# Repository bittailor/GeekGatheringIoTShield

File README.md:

Geek Gathering IoT Shield
==========================

Arduino Sketch and hardware designs (Eagle schematic and board) for the Geek Gathering IoT Shield node.

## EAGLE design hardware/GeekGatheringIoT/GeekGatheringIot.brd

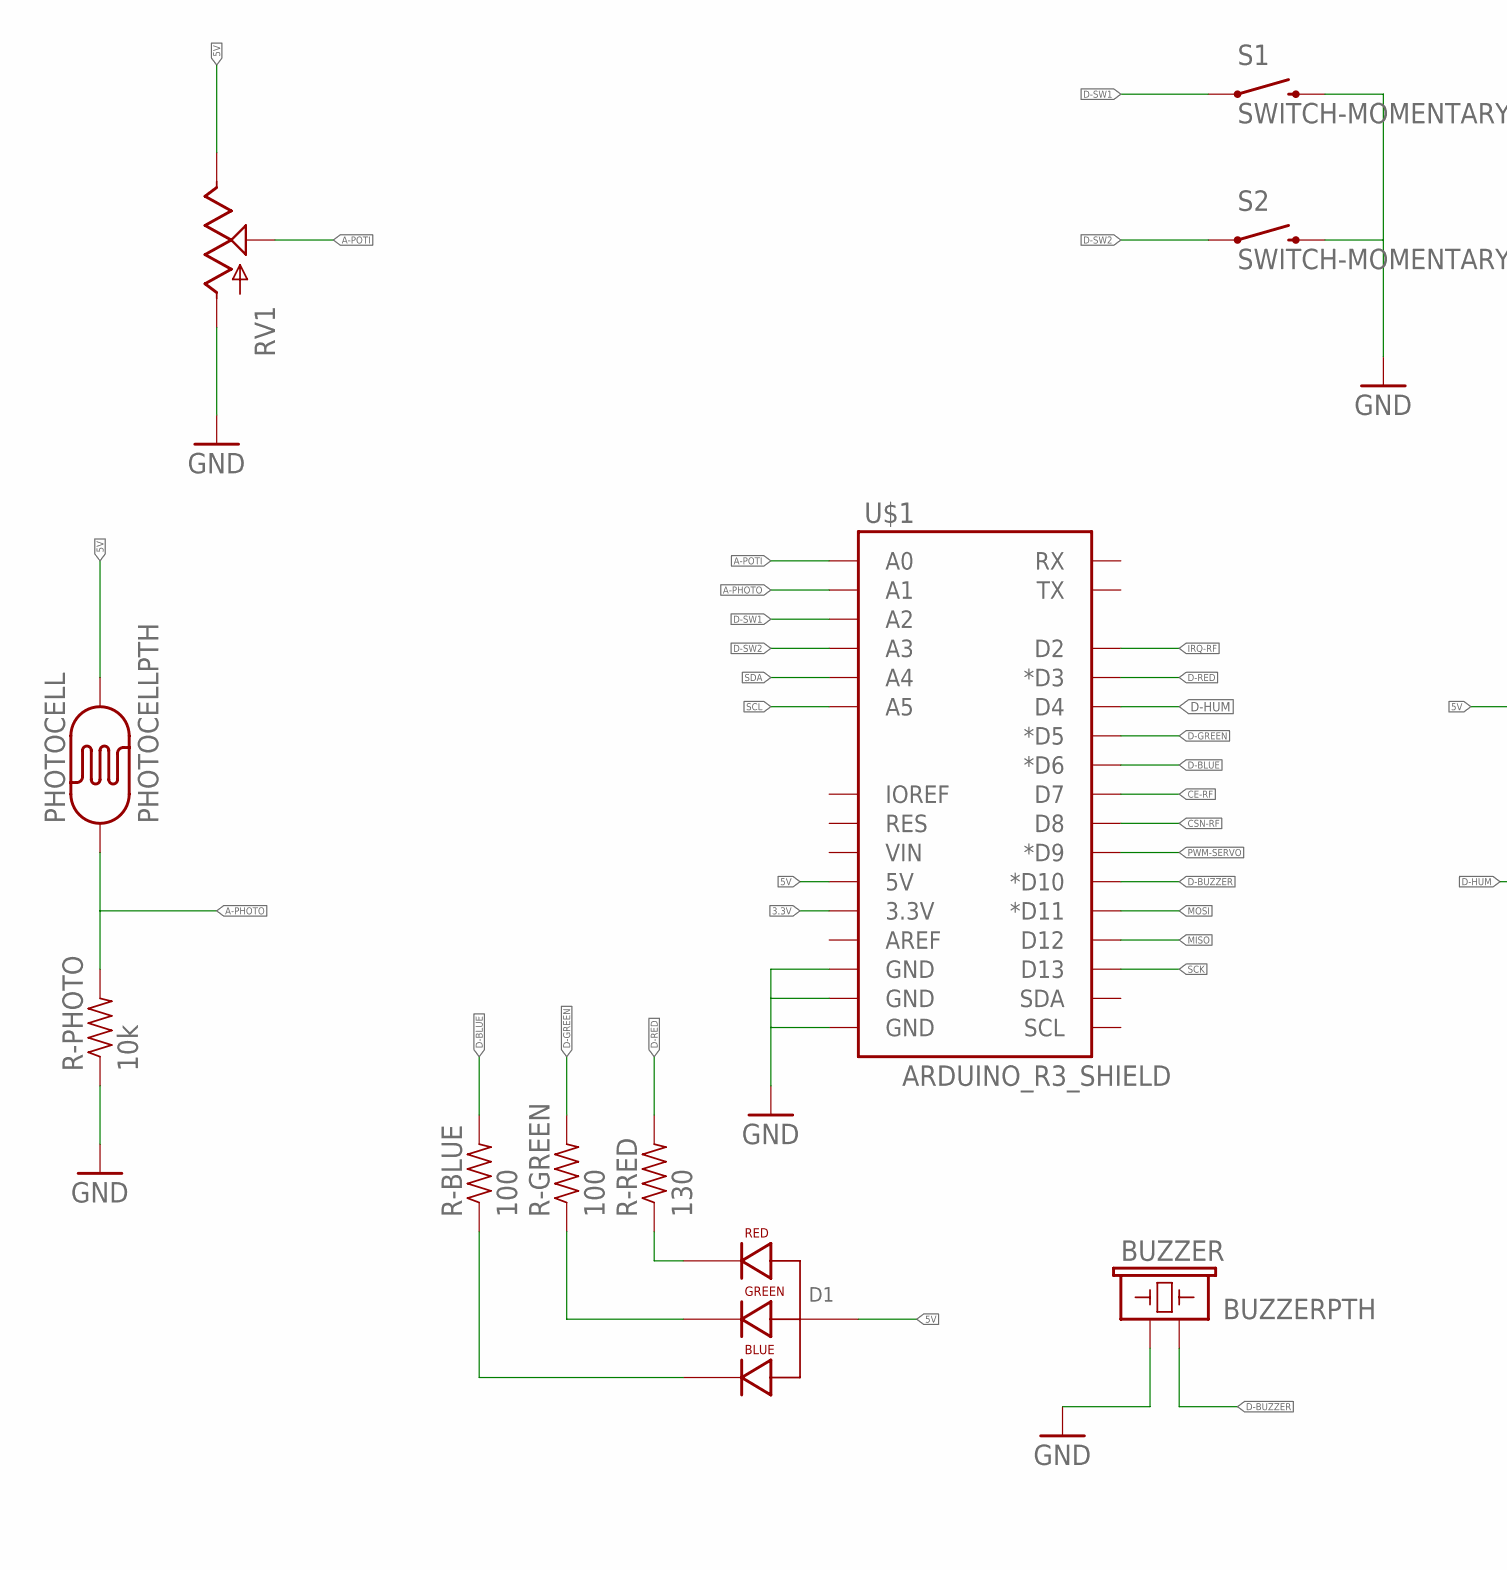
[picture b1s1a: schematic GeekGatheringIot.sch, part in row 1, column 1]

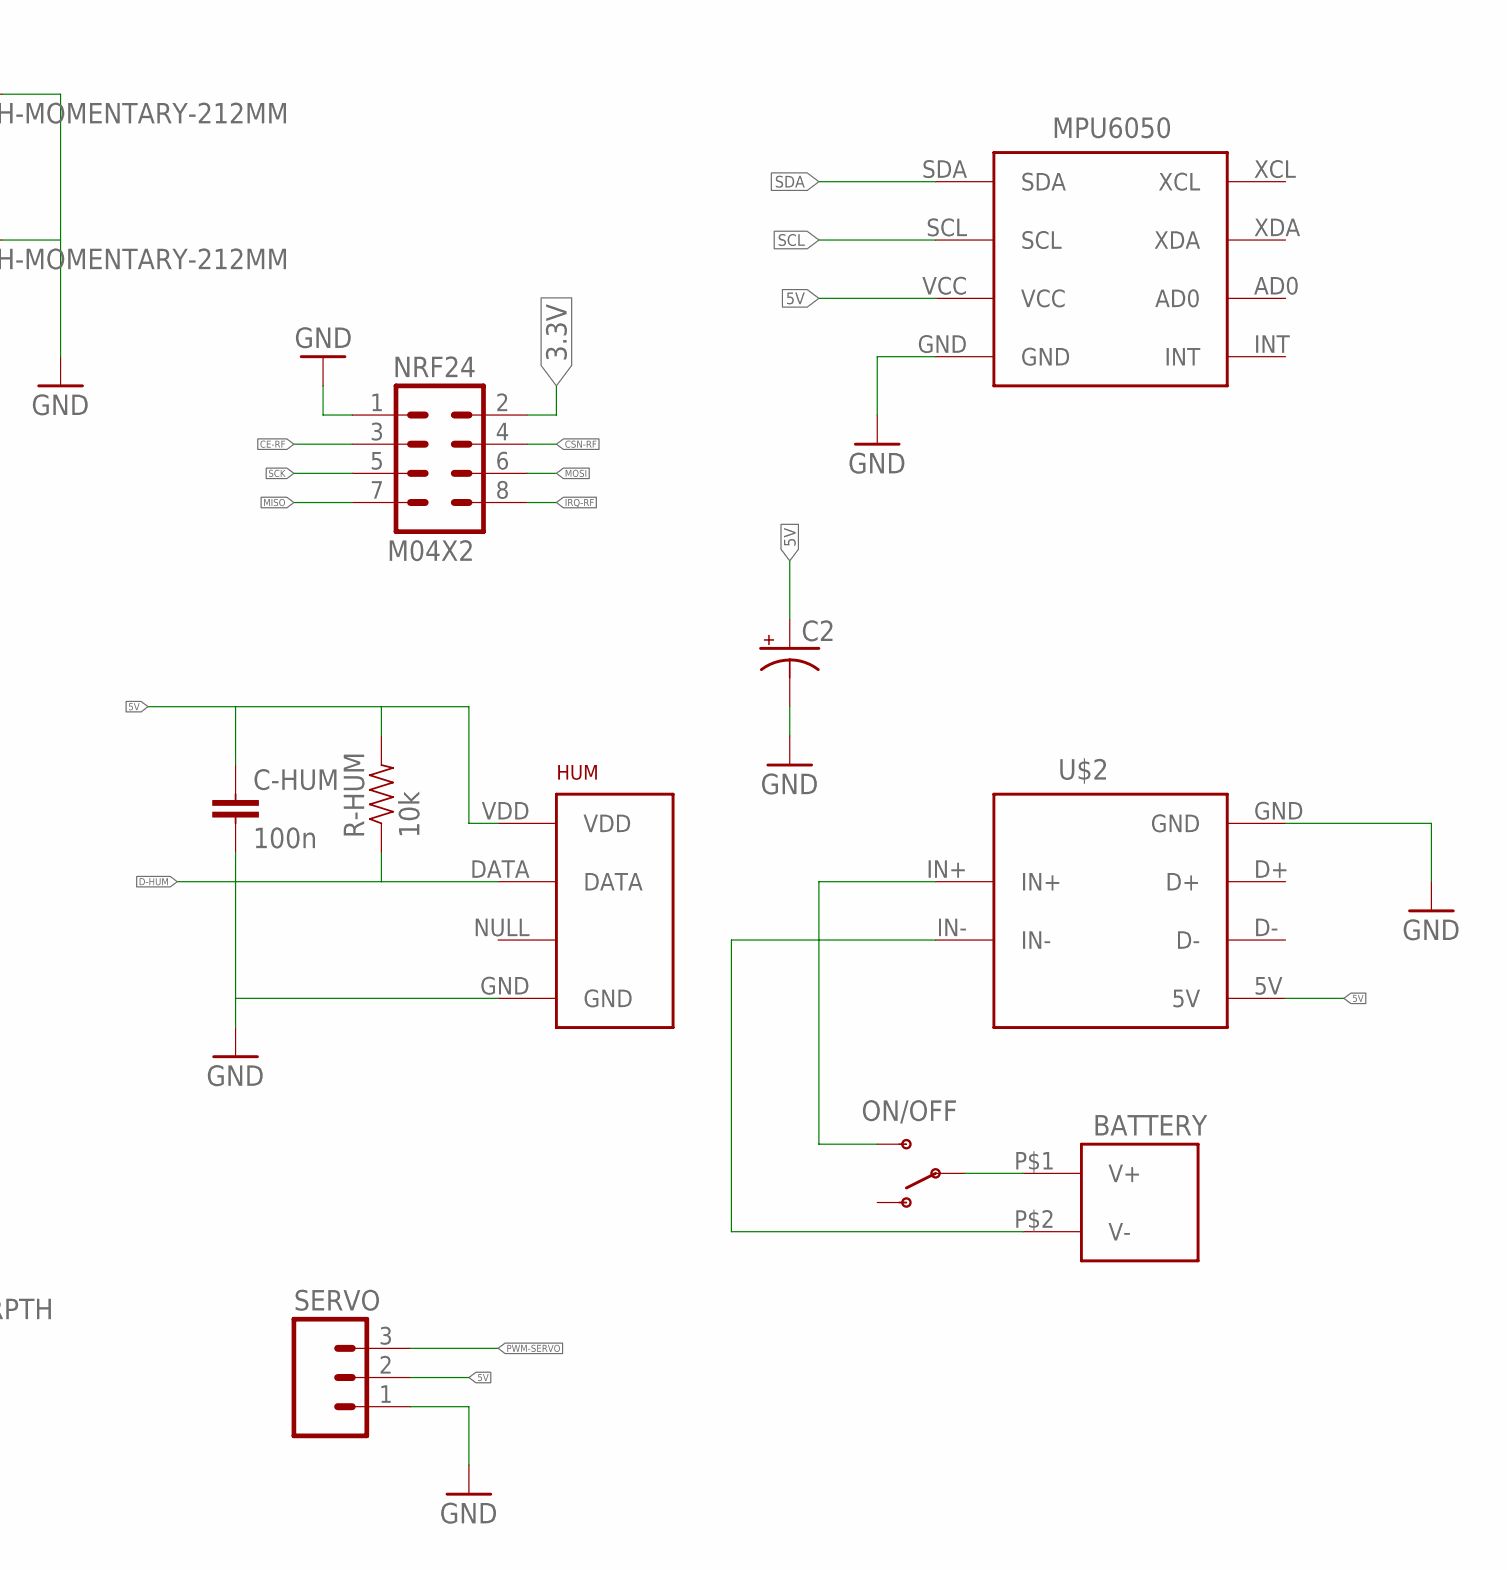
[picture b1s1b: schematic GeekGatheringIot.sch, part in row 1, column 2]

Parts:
BATTERY: BATTERY-PACKAAA; BATTERY-PACK
BUZZER: BUZZERPTH; BUZZER-12MM
C2: CAP_POLPTH2; CPOL-RADIAL-10UF-25V
C-HUM: 100n; CAP-PTH-SMALL
D1: LED-RGB-CA-THRUCLEAR; LED-RGB-THRU
HUM: RHT03_DHT-22_AM2302; RHT03_DHT-22
MPU6050: MPU6050
NRF24: M04X2; 2X4
ON/OFF: SWITCH-SPDTPTH; SWITCH-SPDT
PHOTOCELL: PHOTOCELLPTH; PHOTOCELL
R-BLUE: 100; AXIAL-0.5
R-GREEN: 100; AXIAL-0.5
R-HUM: 10k; AXIAL-0.5
R-PHOTO: 10k; AXIAL-0.5
R-RED: 130; AXIAL-0.5
RV1: POT-RV16AF-20; POT_ALPHA_RV16AF-20
S1, S2: SWITCH-MOMENTARY-212MM; TACTILE-PTH-12MM
SERVO: M03PTH; 1X03
U$1: ARDUINO_R3_SHIELD; UNO_R3_SHIELD
U$2: DC-DC-5V

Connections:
3.3V: NRF24.2, U$1.3.3V
5V: C2.1 (+), C-HUM.1, D1.2 (ANODE), HUM.VDD, MPU6050.VCC, PHOTOCELL.2, R-HUM.P$2 (2), RV1.3 (E), SERVO.2, U$1.5V, U$2.5V
A-PHOTO: PHOTOCELL.1, R-PHOTO.P$2 (2), U$1.A1
A-POTI: RV1.2 (S), U$1.A0
CE-RF: NRF24.3, U$1.D7
CSN-RF: NRF24.4, U$1.D8
D-BLUE: R-BLUE.P$2 (2), U$1.D6 (*D6)
D-BUZZER: BUZZER.- (2), U$1.D10 (*D10)
D-GREEN: R-GREEN.P$2 (2), U$1.D5 (*D5)
D-HUM: HUM.DATA, R-HUM.P$1 (1), U$1.D4
D-RED: R-RED.P$2 (2), U$1.D3 (*D3)
D-SW1: S1.1, U$1.A2
D-SW2: S2.1, U$1.A3
GND: BUZZER.+ (1), C2.2 (-), C-HUM.2, HUM.GND, MPU6050.GND, NRF24.1, R-PHOTO.P$1 (1), RV1.1 (A), S1.3 (2), S2.3 (2), SERVO.1, U$1.GND@0 (GND), U$1.GND@1 (GND), U$1.GND@2 (GND), U$2.GND
IRQ-RF: NRF24.8, U$1.D2
MISO: NRF24.7, U$1.D12
MOSI: NRF24.6, U$1.D11 (*D11)
unnamed: D1.1 (RED_CATHODE), R-RED.P$1 (1)
unnamed: D1.3 (GREEN_CATHODE), R-GREEN.P$1 (1)
unnamed: D1.4 (BLUE_CATHODE), R-BLUE.P$1 (1)
unnamed: BATTERY.P$1 (V+), ON/OFF.2
unnamed: BATTERY.P$2 (V-), U$2.IN-
unnamed: ON/OFF.3 (S), U$2.IN+
PWM-SERVO: SERVO.3, U$1.D9 (*D9)
SCK: NRF24.5, U$1.D13
SCL: MPU6050.SCL, U$1.A5
SDA: MPU6050.SDA, U$1.A4

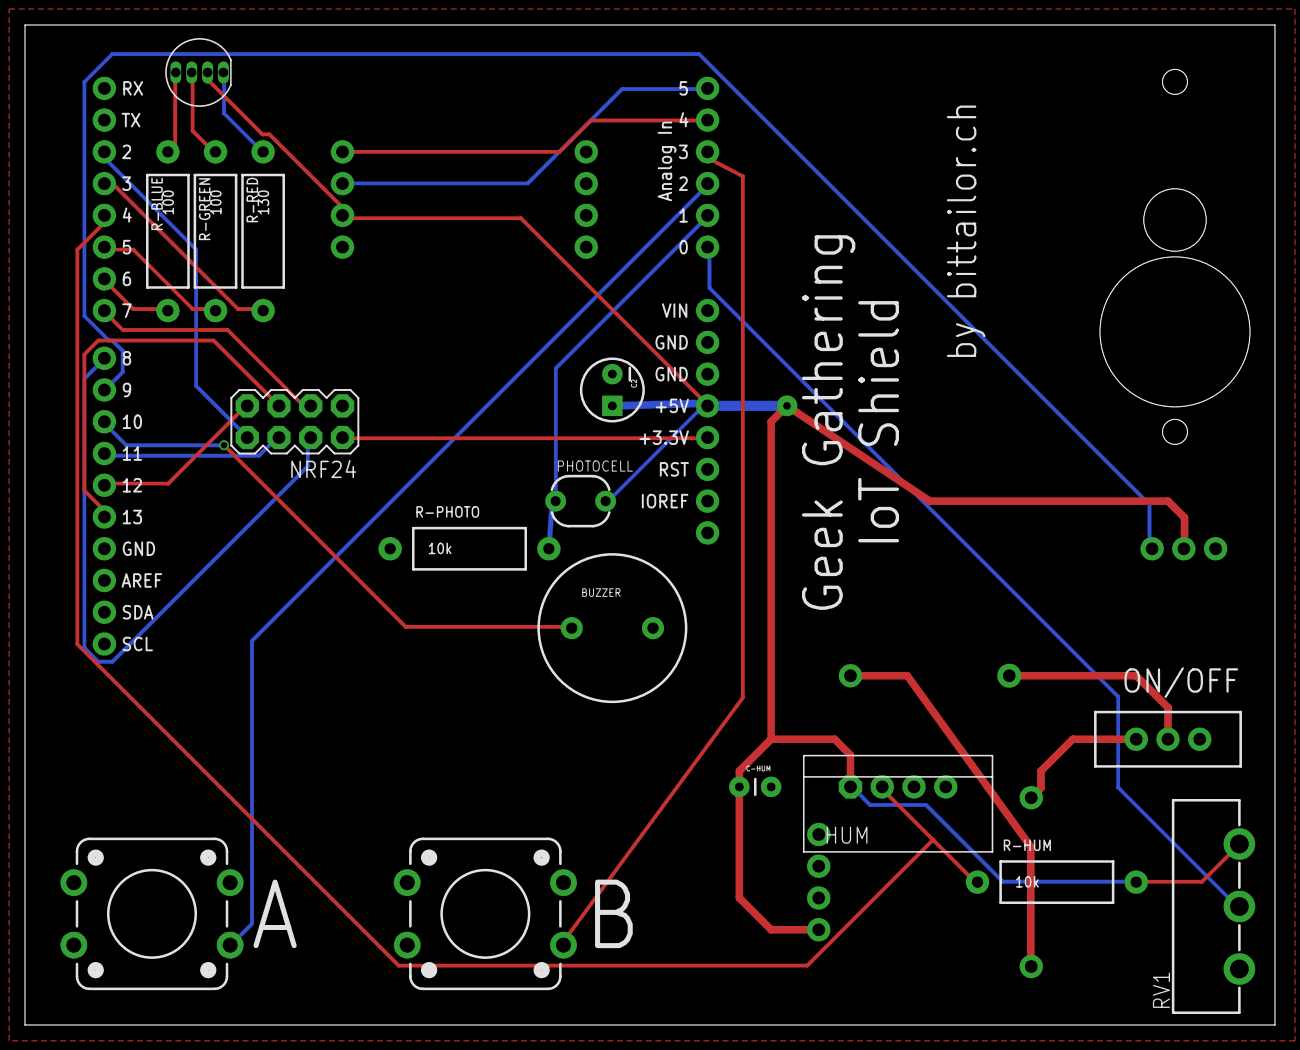
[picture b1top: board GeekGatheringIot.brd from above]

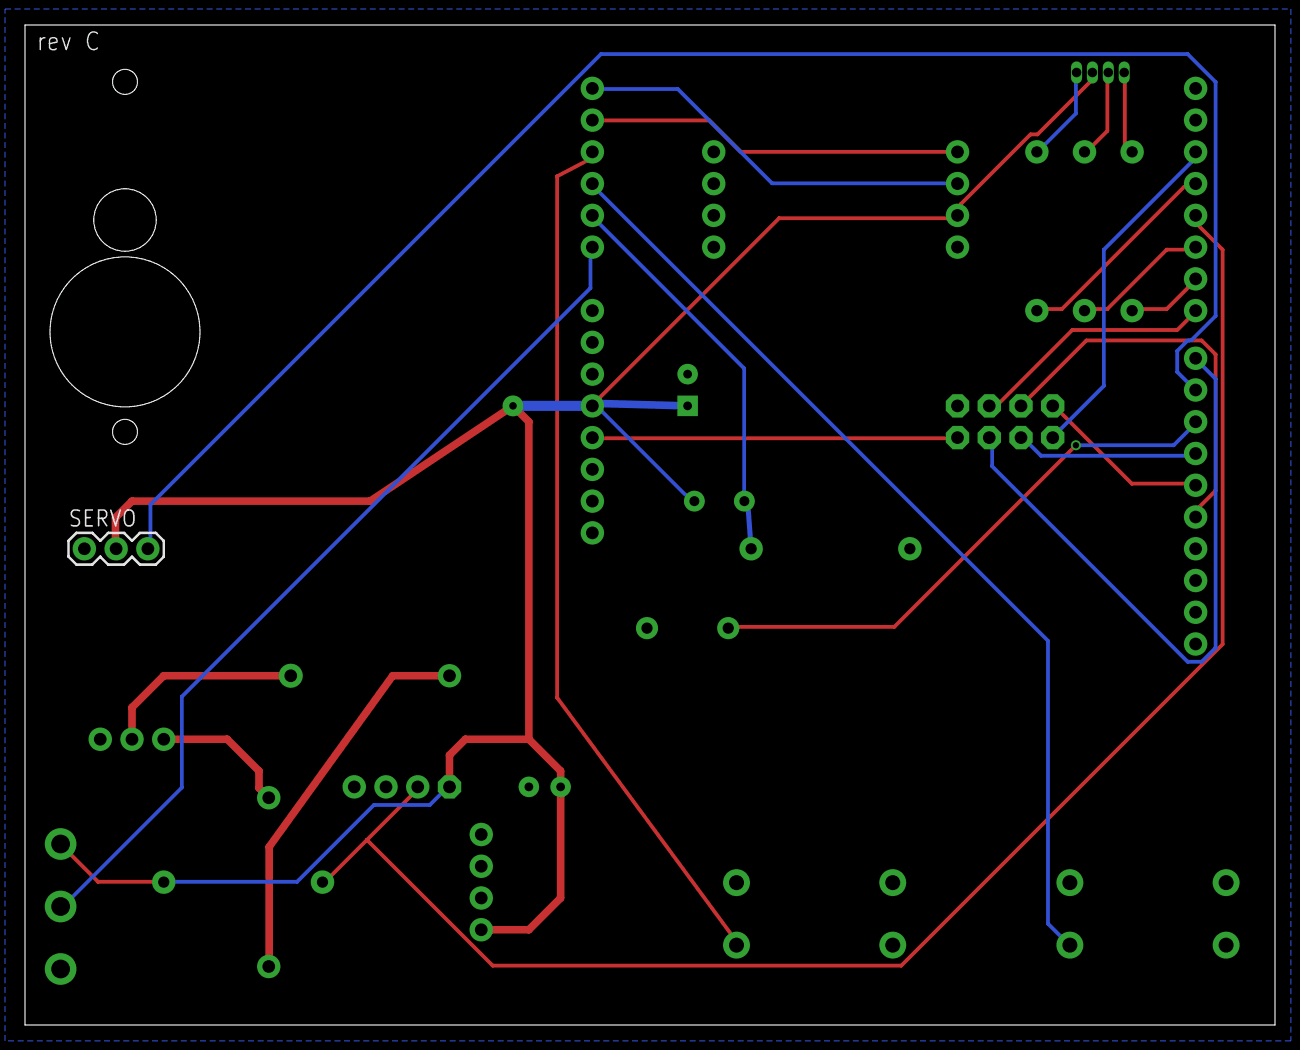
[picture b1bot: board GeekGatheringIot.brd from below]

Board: 2 copper layers, 100.0 x 80.0 mm, 21 parts (3 on the bottom side), 27 nets.

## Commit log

2014-12-20 Initial Arduino sketch code.
2014-12-20 Initial Eagle schematic and board design.
2014-12-20 Update read
2014-12-21 Publisher class for gyro.
2015-01-09 clean-up

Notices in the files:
parts and their libraries:
SparkFun-Capacitors: Licensing: Creative Commons ShareAlike 4.0 International - https://creativecommons.org/licenses/by-sa/4.0
